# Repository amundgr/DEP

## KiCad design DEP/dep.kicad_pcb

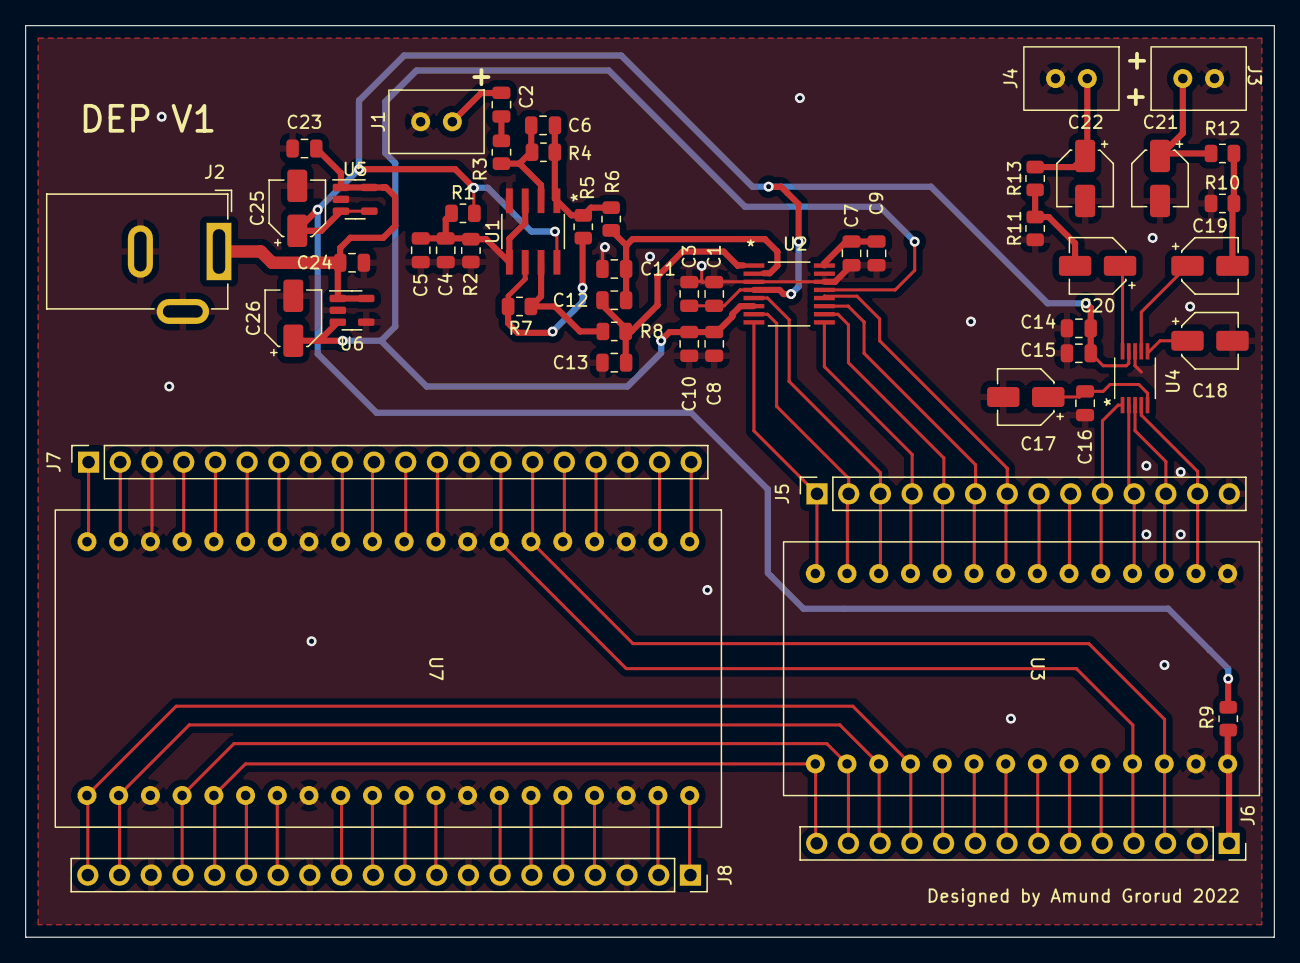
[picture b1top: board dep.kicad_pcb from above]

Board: 2 copper layers, 100.0 x 73.0 mm, 54 parts (0 on the bottom side), 74 nets.

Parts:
C1, C2, C4, C9, C10: 10uF; C_0805_2012Metric
C3, C5, C7, C8, C15, C16, C23, C24: 0.1uF; C_0805_2012Metric
C6: ?; C_0805_2012Metric
C11, C13: 100pF; C_0805_2012Metric
C12: 0.022uF; C_0805_2012Metric
C14: 1uF; C_0805_2012Metric
C17, C19, C20: 3.3uF; CP_Elec_4x3
C18: 10uF; CP_Elec_4x3
C21, C22: ?; CP_Elec_4x3
C25, C26: 4.7uF; CP_Elec_4x3
J1, J3, J4: AudioJack2; Audio Jack Row
J2: Barrel_Jack_Switch; BarrelJack_GCT_DCJ200-10-A_Horizontal
J5, J6: Conn_01x14; PinSocket_1x14_P2.54mm_Vertical
J7, J8: Conn_01x20; PinSocket_1x20_P2.54mm_Vertical
R1, R2, R10, R11: 10k; R_0805_2012Metric
R3, R4: ?; R_0805_2012Metric
R5, R7: 2.49k; R_0805_2012Metric
R6, R8: 40.2k; R_0805_2012Metric
R9: 0; R_0805_2012Metric
R12, R13: 470; R_0805_2012Metric
U1: OPA2134; OPA2134UAE4
U2: PCM4201PWR
U3: TinyFPGA_BX; TinyFPGA BX
U4: CS4345-CZZ
U5, U6: MAX1615xUK; SOT-23-5
U7: Raspberry_Pi_Pico; Raspberry Pi Pico

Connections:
+3V3: C8.2, C10.2, C26.1, U2.6 (S/*M), U2.13 (VDD), U6.3 (OUT)
+5V: C1.2, C3.2, C14.1, C15.1, C25.1, R1.2, R9.1, U1.8 (V+), U2.4 (VCC), U4.9 (VA), U5.3 (OUT), U5.4 (5/~3)
/9Vin: C23.1, C24.1, J2.1, U5.1 (IN), U5.5 (~SHDN), U6.1 (IN), U6.5 (~SHDN)
/FPGA/BCK: J5.6, U2.11 (BCK), U3.8
/FPGA/DATA: J5.4, U2.9 (DATA), U3.10
/FPGA/FPGA_GPIO_5: J5.9, U3.5
/FPGA/FPGA_GPIO_6: J5.8, U3.6
/FPGA/FPGA_GPIO_18: J6.10, U3.18
/FPGA/FPGA_GPIO_19: J6.9, U3.19
/FPGA/FPGA_GPIO_20: J6.8, U3.20
/FPGA/FPGA_GPIO_21: J6.7, U3.21
/FPGA/FPGA_GPIO_22: J6.6, U3.22
/FPGA/FPGA_GPIO_23: J6.5, U3.23
/FPGA/FPGA_Vin: J6.1, R9.2, U3.27 (Vin)
/FPGA/FSYNC: J5.5, U2.10 (FSYNC), U3.9
/FPGA/HPFD: J5.1, U2.8 (HPFD), U3.13
/FPGA/LRCK: J5.12, U3.2, U4.3 (LRCK)
/FPGA/MCLK: J5.13, U3.1, U4.4 (MCLK)
/FPGA/RATE: J5.3, U2.5 (RATE), U3.11
/FPGA/SCKID: J5.7, U2.12 (SCKI), U3.7
/FPGA/SCL: J6.4, J7.14, U3.24, U7.6 (GP5)
/FPGA/SDA: J6.3, J7.15, U3.25 (3v3), U7.5 (GP4)
/FPGA/SDIN: J5.10, U3.4, U4.1 (SDIN)
/FPGA/SPI_CIPO: J6.11, J8.20, U3.17, U7.20 (GP16)
/FPGA/SPI_CS: J6.12, J8.19, U3.16, U7.21 (GP17)
/FPGA/SPI_POCI: J6.14, J8.16, U3.14, U7.24 (GP19)
/FPGA/SPI_SCK: J6.13, J8.17, U3.15, U7.23 (GP18)
/FPGA/~DEM/SCLK: J5.11, U3.3, U4.2 (*DEM/SCLK)
/FPGA/~RST: J5.2, U2.7 (*RST), U3.12
/Input/2V5_reference_input_stage: C4.2, C5.2, R1.1, R2.2, U1.3 (+), U1.5 (+)
/Input/OPamp_1_output: C6.2, R4.2, R5.2, R6.1, U1.1
/Input/OPamp_1_positive_input: C6.1, R3.2, R4.1, U1.2 (-)
/Input/OPamp_2_output: R7.2, R8.1, U1.7
/Input/OPamp_2_positive_input: R5.1, R7.1, U1.6 (-)
/Input/Vin+: C12.1, C13.2, R8.2, U2.1 (VIN+)
/Input/Vin-: C11.1, C12.2, R6.2, U2.2 (VIN-)
/MCU/MCU_3V3_EN: J8.4, U7.36 (3V3_EN)
/MCU/MCU_ADC_VREF: J8.6, U7.34 (ADC_VREF)
/MCU/MCU_GP0: J7.20, U7.0 (GP0)
/MCU/MCU_GP1: J7.19, U7.1 (GP1)
/MCU/MCU_GP2: J7.17, U7.3 (GP2)
/MCU/MCU_GP3: J7.16, U7.4 (GP3)
/MCU/MCU_GP6: J7.12, U7.8 (GP6)
/MCU/MCU_GP7: J7.11, U7.9 (GP7)
/MCU/MCU_GP8: J7.10, U7.10 (GP8)
/MCU/MCU_GP9: J7.9, U7.11 (GP9)
/MCU/MCU_GP10: J7.7, U7.13 (G10)
/MCU/MCU_GP11: J7.6, U7.14 (G11)
/MCU/MCU_GP12: J7.5, U7.15 (G12)
/MCU/MCU_GP13: J7.4, U7.16 (G13)
/MCU/MCU_GP14: J7.2, U7.18 (GP14)
/MCU/MCU_GP15: J7.1, U7.19 (GP15)
/MCU/MCU_GP20: J8.15, U7.25 (GP20)
/MCU/MCU_GP21: J8.14, U7.26 (GP21)
/MCU/MCU_GP22: J8.12, U7.28 (GP22)
/MCU/MCU_GP26: J8.10, U7.30 (GP26)
/MCU/MCU_GP27: J8.9, U7.31 (GP27)
/MCU/MCU_GP28: J8.7, U7.33 (GP28)
/MCU/MCU_RUN: J8.11, U7.29 (RUN)
/MCU/MCU_VBUS: J8.1, U7.39 (VBUS)
/MCU/MCU_VSYS: J8.2, U7.38 (VSYS)
/MCU/MC_3V3: J8.5, U7.35 (3V3)
/Output/DAC_FILT+: C18.1, U4.6 (FILT+)
/Output/DAC_OUT_L: C19.1, U4.7 (AOUTL)
/Output/DAC_OUT_R: C20.1, U4.10 (AOUTR)
/Output/DAC_VQ: C16.2, C17.1, U4.5 (VQ)
/Output/HeadphoneOut: C22.1, J4.S, R13.2
/Output/PedalOut: C21.1, J3.S, R12.2
/signal_in: C2.1, J1.S
GND: C1.1, C3.1, C4.1, C5.1, C7.2, C8.1, C9.2, C10.1, C11.2, C13.1, C14.2, C15.2, C16.1, C17.2, C18.2, C21.2, C22.2, C23.2, C24.2, C25.2, C26.2, J1.T, J2.2, J2.3, J3.T, J4.T, J5.14, J6.2, J7.3, J7.8, J7.13, J7.18, J8.3, J8.8, J8.13, J8.18, R2.1, R10.1, R11.1, U1.4 (V-), U2.3 (AGND), U2.14 (DGND), U2.15 (VREF-), U3.0 (GND), U3.26 (GND), U4.8 (GND), U5.2 (GND), U6.2 (GND), U6.4 (5/~3), U7.2 (GND), U7.7 (GND), U7.12 (GND), U7.17 (GND), U7.22 (GND), U7.27 (GND), U7.32 (AGND), U7.37 (GND)
unnamed: C2.2, R3.1
unnamed: C7.1, C9.1, U2.16 (VREF+)
unnamed: C19.2, R10.2, R12.1
unnamed: C20.2, R11.2, R13.1

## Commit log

2022-03-21 update .gitignore again...
2022-03-21 DEP V1
2022-04-06 fix +/- op-amp error...

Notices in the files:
parts and their libraries:
Copyright 2021 Accelerated Designs. All rights reserved.
